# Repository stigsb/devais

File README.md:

# Devais - Handheld AI Assistant Device

A battery-powered, pocket-sized AI assistant with a push-to-talk interface. Designed as a walkie-talkie style device that solves the common problem of AI apps responding to hesitation during speech.

## Overview

**Form Factor:** Stick-shaped handheld device (~30x30x150mm)  
**Power:** 18650 battery with USB-C charging  
**Interface:** Push-to-talk button, status LEDs, speaker and microphone  
**Connectivity:** Bluetooth Low Energy (nRF52840)

## Hardware Components

### Core Controller
- **Seeed XIAO nRF52840** - Ultra-low power microcontroller with BLE
  - Superior battery efficiency vs ESP32 alternatives
  - 20.8 days idle battery life (vs 8.3 days for ESP32-C3)
  - 5 days continuous audio streaming (vs 27 hours for ESP32-C3)

### Audio System (I2S Bus Architecture)
- **INMP441** - MEMS I2S microphone
- **MAX98357A** - I2S Class D amplifier
- Compact speaker
- Shared clock signals with separate data lines for efficiency

### User Interface
- Tactile push-to-talk button
- Power/mode button
- Status LEDs (power, connectivity, activity)

### Power
- 18650 Li-ion battery
- USB-C charging port
- Efficient power management optimized for audio streaming

## Project Structure

```
devais/
├── cad/              # 3D CAD models (CadQuery scripts)
├── firmware/         # nRF52840 firmware
├── docs/             # Documentation, wiring diagrams
├── hardware/         # PCB designs, schematics
└── README.md
```

## Getting Started

### Prerequisites
- Python 3.14
- uv (Python package manager)
- Prusa MK3S or compatible 3D printer

### Installation

```bash
# Clone the repository
git clone https://github.com/stigsb/devais.git
cd devais

# Install dependencies with uv
uv sync

# Activate virtual environment
source .venv/bin/activate  # Linux/Mac
# or
.venv\Scripts\activate     # Windows
```

### Running CAD Scripts

```bash
# Generate the enclosure model
python cad/enclosure.py

# Output will be in cad/output/ as STL files
```

## Design Principles

1. **Intentional Interaction** - Push-to-talk prevents accidental triggers and hesitation issues
2. **Battery Efficiency** - Component selection optimized for multi-day battery life
3. **Pocket Portability** - Narrow form factor fits comfortably in pocket or hand
4. **Programmatic CAD** - Python-based modeling enables iterative design and parameter adjustment

## Status

- [x] Component selection and power analysis
- [x] I2S audio architecture design
- [x] Wiring diagram and pin assignments
- [ ] 3D enclosure design (in progress)
- [ ] PCB layout
- [ ] Firmware development
- [ ] Prototype assembly

## Location

Trondheim, Norway

## License

TBD

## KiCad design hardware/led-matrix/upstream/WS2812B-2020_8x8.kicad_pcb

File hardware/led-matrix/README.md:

# LED matrix daughterboard

**Status: deferred to V2.** V1 ships the existing two 3 mm LED openings. Nothing
here is on the V1 build path.

A higher-fidelity replacement for the 2x WS2812B-2020 indicator board, for
signalling the state of several concurrent agents. Background, part selection,
cost and the rejected alternatives are in
[`docs/led-indicator-research-2026-09-13.md`](../../docs/led-indicator-research-2026-09-13.md).

## upstream/

Third-party KiCad 7 design, taken as a starting point — not a devais board.

- Source: Arduino Forum, "Showcase: PCB for 8x8 matrix of WB2812B-2020"
  <https://forum.arduino.cc/t/showcase-pcb-for-8x8-matrix-of-wb2812b-2020/1154180>
- Licence: not stated by the author. Resolve before publishing a derived board.
- As drawn: 25.0 x 25.0 mm, 2 layers, 8x8 on a 3.0 mm pitch (21 mm LED field),
  64x `MR_LED:WS2812B2020`, 2x `MR_Connect:DS1024-1x3R0` 3-pin daisy-chain
  connectors, no decoupling capacitors.

## Required changes for devais

- **LED part:** WS2812B-2020-V6 (LCSC C52917434), not the V1.3 part the upstream
  footprint was drawn for. V6 is spec'd 3.3-5.3 V and <=1 uA idle, so it runs
  directly off the 18650 with no boost and needs no power gate. Verify the V6
  recommended land pattern against the upstream footprint before reuse.
- **Connector:** one 3-pin JST matching the existing J_LED cable (VDD_LED, GND,
  LED_DATA), replacing both DS1024 daisy-chain connectors.
- **Decoupling:** upstream has none. Add local capacitors.
- **Outline:** 25 mm is the enclosure's hard limit at the front flat face
  (`LONG_SIDE_LENGTH` ~= 24.9 mm). Shrinking the pitch to 2.5 mm gives a 20 mm
  field and working margin.

## Open questions

- Front-face split: the enclosure parts at X = 0 and the current LED openings sit
  entirely on the chassis half. A centred 25 mm board crosses the joint.
- Diffusion: at 2.5-3.0 mm pitch behind the 1.6 mm wall, per-pixel separation
  needs a grid insert. A plain window blends adjacent pixels into a blur.
- Brightness cap: 64 LEDs at full white is ~2.3 A. Firmware must limit global
  brightness.

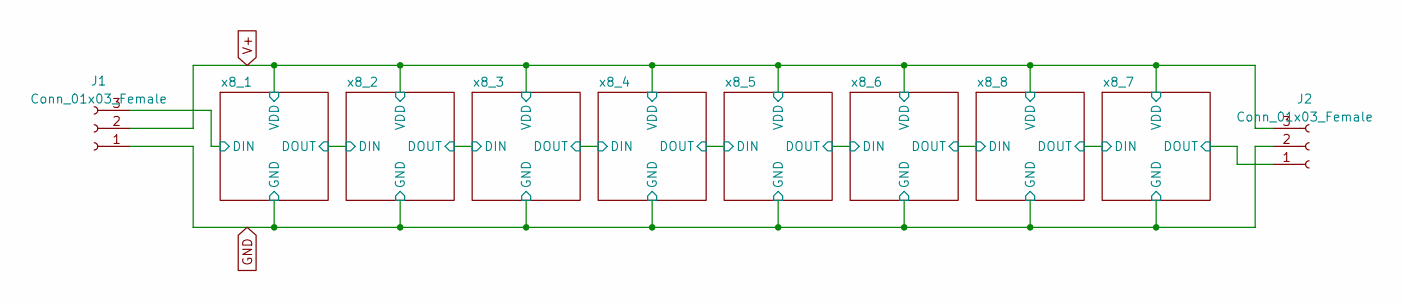
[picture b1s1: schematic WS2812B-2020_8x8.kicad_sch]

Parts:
J1, J2: Conn_01x03_Female; DS1024-1x3R0 01x03

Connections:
/x8_1/DIN: J1.3; also elsewhere on the board
/x8_7/DOUT: J2.1; also elsewhere on the board
GND: J1.1, J2.2; also elsewhere on the board
V+: J1.2, J2.3; also elsewhere on the board

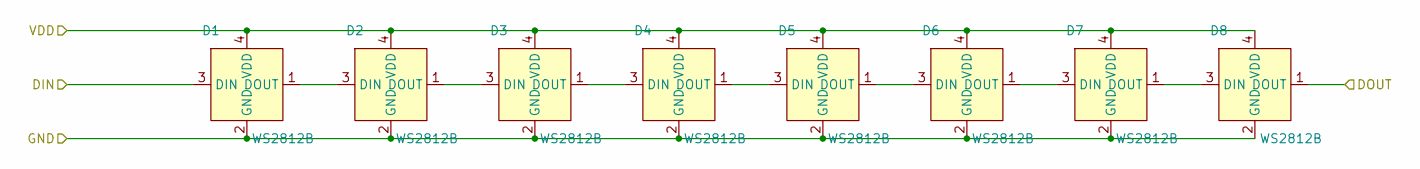
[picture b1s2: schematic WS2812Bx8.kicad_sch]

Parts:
D1, D2, D3, D4, D5, D6, D7, D8: WS2812B; WS2812B2020

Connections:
/x8_1/DIN: D1.3 (DIN); also elsewhere on the board
/x8_1/DOUT: D8.1 (DOUT); also elsewhere on the board
GND: D1.2 (GND), D2.2 (GND), D3.2 (GND), D4.2 (GND), D5.2 (GND), D6.2 (GND), D7.2 (GND), D8.2 (GND); also elsewhere on the board
unnamed: D1.1 (DOUT), D2.3 (DIN)
unnamed: D2.1 (DOUT), D3.3 (DIN)
unnamed: D3.1 (DOUT), D4.3 (DIN)
unnamed: D4.1 (DOUT), D5.3 (DIN)
unnamed: D5.1 (DOUT), D6.3 (DIN)
unnamed: D6.1 (DOUT), D7.3 (DIN)
unnamed: D7.1 (DOUT), D8.3 (DIN)
V+: D1.4 (VDD), D2.4 (VDD), D3.4 (VDD), D4.4 (VDD), D5.4 (VDD), D6.4 (VDD), D7.4 (VDD), D8.4 (VDD); also elsewhere on the board

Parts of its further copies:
D9, D10, D11, D12, D13, D14, D15, D16, D17, D18, D19, D20, D21, D22, D23, D24, D25, D26, D27, D28, D29, D30, D31, D32, D33, D34, D35, D36, D37, D38, D39, D40, D41, D42, D43, D44, D45, D46, D47, D48, D49, D50, D51, D52, D53, D54, D55, D56, D57, D58, D59, D60, D61, D62, D63, D64: WS2812B; WS2812B2020

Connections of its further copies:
/x8_1/DOUT: D9.3 (DIN); also elsewhere on the board
/x8_2/DOUT: D16.1 (DOUT), D17.3 (DIN)
/x8_3/DOUT: D24.1 (DOUT), D25.3 (DIN)
/x8_4/DOUT: D32.1 (DOUT), D33.3 (DIN)
/x8_5/DOUT: D40.1 (DOUT), D41.3 (DIN)
/x8_6/DOUT: D48.1 (DOUT), D49.3 (DIN)
/x8_7/DIN: D56.1 (DOUT), D57.3 (DIN)
/x8_7/DOUT: D64.1 (DOUT); also elsewhere on the board
GND: D9.2 (GND), D10.2 (GND), D11.2 (GND), D12.2 (GND), D13.2 (GND), D14.2 (GND), D15.2 (GND), D16.2 (GND), D17.2 (GND), D18.2 (GND), D19.2 (GND), D20.2 (GND), D21.2 (GND), D22.2 (GND), D23.2 (GND), D24.2 (GND), D25.2 (GND), D26.2 (GND), D27.2 (GND), D28.2 (GND), D29.2 (GND), D30.2 (GND), D31.2 (GND), D32.2 (GND), D33.2 (GND), D34.2 (GND), D35.2 (GND), D36.2 (GND), D37.2 (GND), D38.2 (GND), D39.2 (GND), D40.2 (GND), D41.2 (GND), D42.2 (GND), D43.2 (GND), D44.2 (GND), D45.2 (GND), D46.2 (GND), D47.2 (GND), D48.2 (GND), D49.2 (GND), D50.2 (GND), D51.2 (GND), D52.2 (GND), D53.2 (GND), D54.2 (GND), D55.2 (GND), D56.2 (GND), D57.2 (GND), D58.2 (GND), D59.2 (GND), D60.2 (GND), D61.2 (GND), D62.2 (GND), D63.2 (GND), D64.2 (GND); also elsewhere on the board
unnamed: D9.1 (DOUT), D10.3 (DIN)
unnamed: D10.1 (DOUT), D11.3 (DIN)
unnamed: D11.1 (DOUT), D12.3 (DIN)
unnamed: D12.1 (DOUT), D13.3 (DIN)
unnamed: D13.1 (DOUT), D14.3 (DIN)
unnamed: D14.1 (DOUT), D15.3 (DIN)
unnamed: D15.1 (DOUT), D16.3 (DIN)
unnamed: D17.1 (DOUT), D18.3 (DIN)
unnamed: D18.1 (DOUT), D19.3 (DIN)
unnamed: D19.1 (DOUT), D20.3 (DIN)
unnamed: D20.1 (DOUT), D21.3 (DIN)
unnamed: D21.1 (DOUT), D22.3 (DIN)
unnamed: D22.1 (DOUT), D23.3 (DIN)
unnamed: D23.1 (DOUT), D24.3 (DIN)
unnamed: D25.1 (DOUT), D26.3 (DIN)
unnamed: D26.1 (DOUT), D27.3 (DIN)
unnamed: D27.1 (DOUT), D28.3 (DIN)
unnamed: D28.1 (DOUT), D29.3 (DIN)
unnamed: D29.1 (DOUT), D30.3 (DIN)
unnamed: D30.1 (DOUT), D31.3 (DIN)
unnamed: D31.1 (DOUT), D32.3 (DIN)
unnamed: D33.1 (DOUT), D34.3 (DIN)
unnamed: D34.1 (DOUT), D35.3 (DIN)
unnamed: D35.1 (DOUT), D36.3 (DIN)
unnamed: D36.1 (DOUT), D37.3 (DIN)
unnamed: D37.1 (DOUT), D38.3 (DIN)
unnamed: D38.1 (DOUT), D39.3 (DIN)
unnamed: D39.1 (DOUT), D40.3 (DIN)
unnamed: D41.1 (DOUT), D42.3 (DIN)
unnamed: D42.1 (DOUT), D43.3 (DIN)
unnamed: D43.1 (DOUT), D44.3 (DIN)
unnamed: D44.1 (DOUT), D45.3 (DIN)
unnamed: D45.1 (DOUT), D46.3 (DIN)
unnamed: D46.1 (DOUT), D47.3 (DIN)
unnamed: D47.1 (DOUT), D48.3 (DIN)
unnamed: D49.1 (DOUT), D50.3 (DIN)
unnamed: D50.1 (DOUT), D51.3 (DIN)
unnamed: D51.1 (DOUT), D52.3 (DIN)
unnamed: D52.1 (DOUT), D53.3 (DIN)
unnamed: D53.1 (DOUT), D54.3 (DIN)
unnamed: D54.1 (DOUT), D55.3 (DIN)
unnamed: D55.1 (DOUT), D56.3 (DIN)
unnamed: D57.1 (DOUT), D58.3 (DIN)
unnamed: D58.1 (DOUT), D59.3 (DIN)
unnamed: D59.1 (DOUT), D60.3 (DIN)
unnamed: D60.1 (DOUT), D61.3 (DIN)
unnamed: D61.1 (DOUT), D62.3 (DIN)
unnamed: D62.1 (DOUT), D63.3 (DIN)
unnamed: D63.1 (DOUT), D64.3 (DIN)
V+: D9.4 (VDD), D10.4 (VDD), D11.4 (VDD), D12.4 (VDD), D13.4 (VDD), D14.4 (VDD), D15.4 (VDD), D16.4 (VDD), D17.4 (VDD), D18.4 (VDD), D19.4 (VDD), D20.4 (VDD), D21.4 (VDD), D22.4 (VDD), D23.4 (VDD), D24.4 (VDD), D25.4 (VDD), D26.4 (VDD), D27.4 (VDD), D28.4 (VDD), D29.4 (VDD), D30.4 (VDD), D31.4 (VDD), D32.4 (VDD), D33.4 (VDD), D34.4 (VDD), D35.4 (VDD), D36.4 (VDD), D37.4 (VDD), D38.4 (VDD), D39.4 (VDD), D40.4 (VDD), D41.4 (VDD), D42.4 (VDD), D43.4 (VDD), D44.4 (VDD), D45.4 (VDD), D46.4 (VDD), D47.4 (VDD), D48.4 (VDD), D49.4 (VDD), D50.4 (VDD), D51.4 (VDD), D52.4 (VDD), D53.4 (VDD), D54.4 (VDD), D55.4 (VDD), D56.4 (VDD), D57.4 (VDD), D58.4 (VDD), D59.4 (VDD), D60.4 (VDD), D61.4 (VDD), D62.4 (VDD), D63.4 (VDD), D64.4 (VDD); also elsewhere on the board

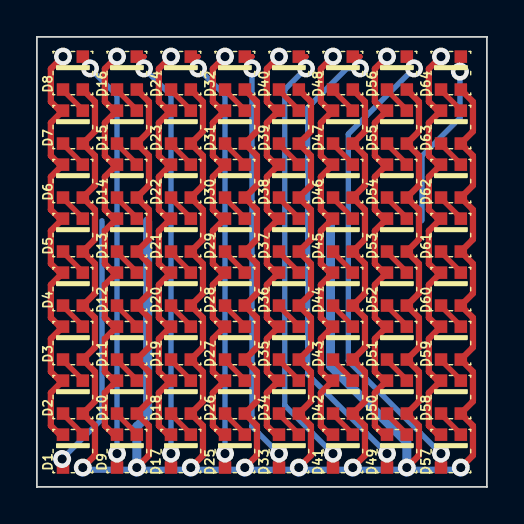
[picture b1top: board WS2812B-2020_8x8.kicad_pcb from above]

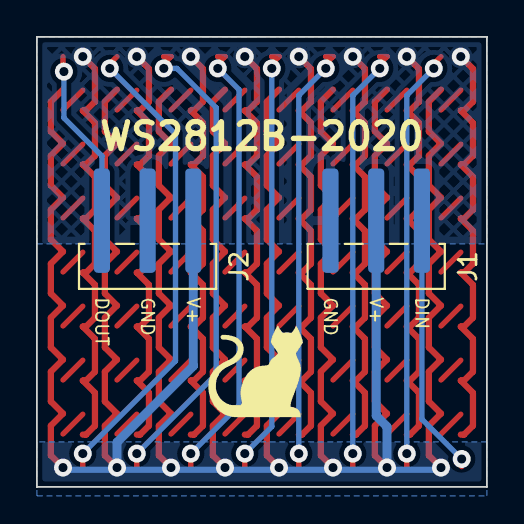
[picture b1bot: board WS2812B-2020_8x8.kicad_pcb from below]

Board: 2 copper layers, 25.0 x 25.0 mm, 66 parts (2 on the bottom side), 67 nets.

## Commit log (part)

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2026-01-03 WiP enclosure + button
2026-01-04 Looking good
2026-01-04 Tweaks to help Gemini one-shot the cad/enclosure.py script
2026-01-04 Move gemini_cad_skill.md to context/, update docs/cad-guide.md
2026-01-04 Add CI workflow for STL viewers
2026-01-04 deploy: a660847aea00ef2913dbf70acb53961509e48f64
2026-01-04 Fix model colours
2026-01-04 deploy: 70580a0aa1a9a81fd4618da171cf8a4189cbcd1a
2026-01-18 Reorganize CAD skill directory and update documentation
    - Rename cad-modeller-skill/ to cad-modeller/ for consistency
    - Add context/README.md index for AI agent context files
    - Update AGENTS.md to reference new skill location
    - Update context/enclosure-work.md with complete implementation status
    - Remove deprecated context/gemini_cad_skill.md
2026-02-08 Re-run with Opus 4.6
2026-04-06 Add snap-fit enclosure redesign spec
    Replace front/back split + threaded lid with left/right snap-fit
    halves. All electronics on chassis half, cover is purely mechanical.
2026-04-06 Add snap-fit enclosure redesign implementation plan
2026-04-06 Remove threaded bottom lid machinery from enclosure
2026-04-06 Close bottom, update LEDs to 2x RGB, shift mic +1mm
    - Hollow starts at WALL_THICKNESS for solid bottom wall
    - 2 WS2812B-2020 LED holes at x=5,11mm (was 3 LEDs centered)
    - Mic hole shifted to x=+1mm for chassis-side placement
2026-04-06 Add battery cradle ribs for 18650 on chassis half
2026-04-06 Rewrite split to X=0 with snap-fit on front/back walls
    Rename halves from front/back to right/left. Move tongue-and-groove
    rails and snap clips from left/right walls to front/back walls. Update
    exported STL filenames to enclosure_right.stl and enclosure_left.stl.
2026-04-06 Update enclosure spec for snap-fit redesign
2026-04-06 PCB generator
2026-04-06 Use tscircuit, redesign PCB, split enclosure across speaker/mic
2026-04-06 PCB broadened to 36mm
2026-04-07 Added PCB mounting holes
